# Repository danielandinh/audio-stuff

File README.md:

# audio-stuff
collection of audio circuits/projects

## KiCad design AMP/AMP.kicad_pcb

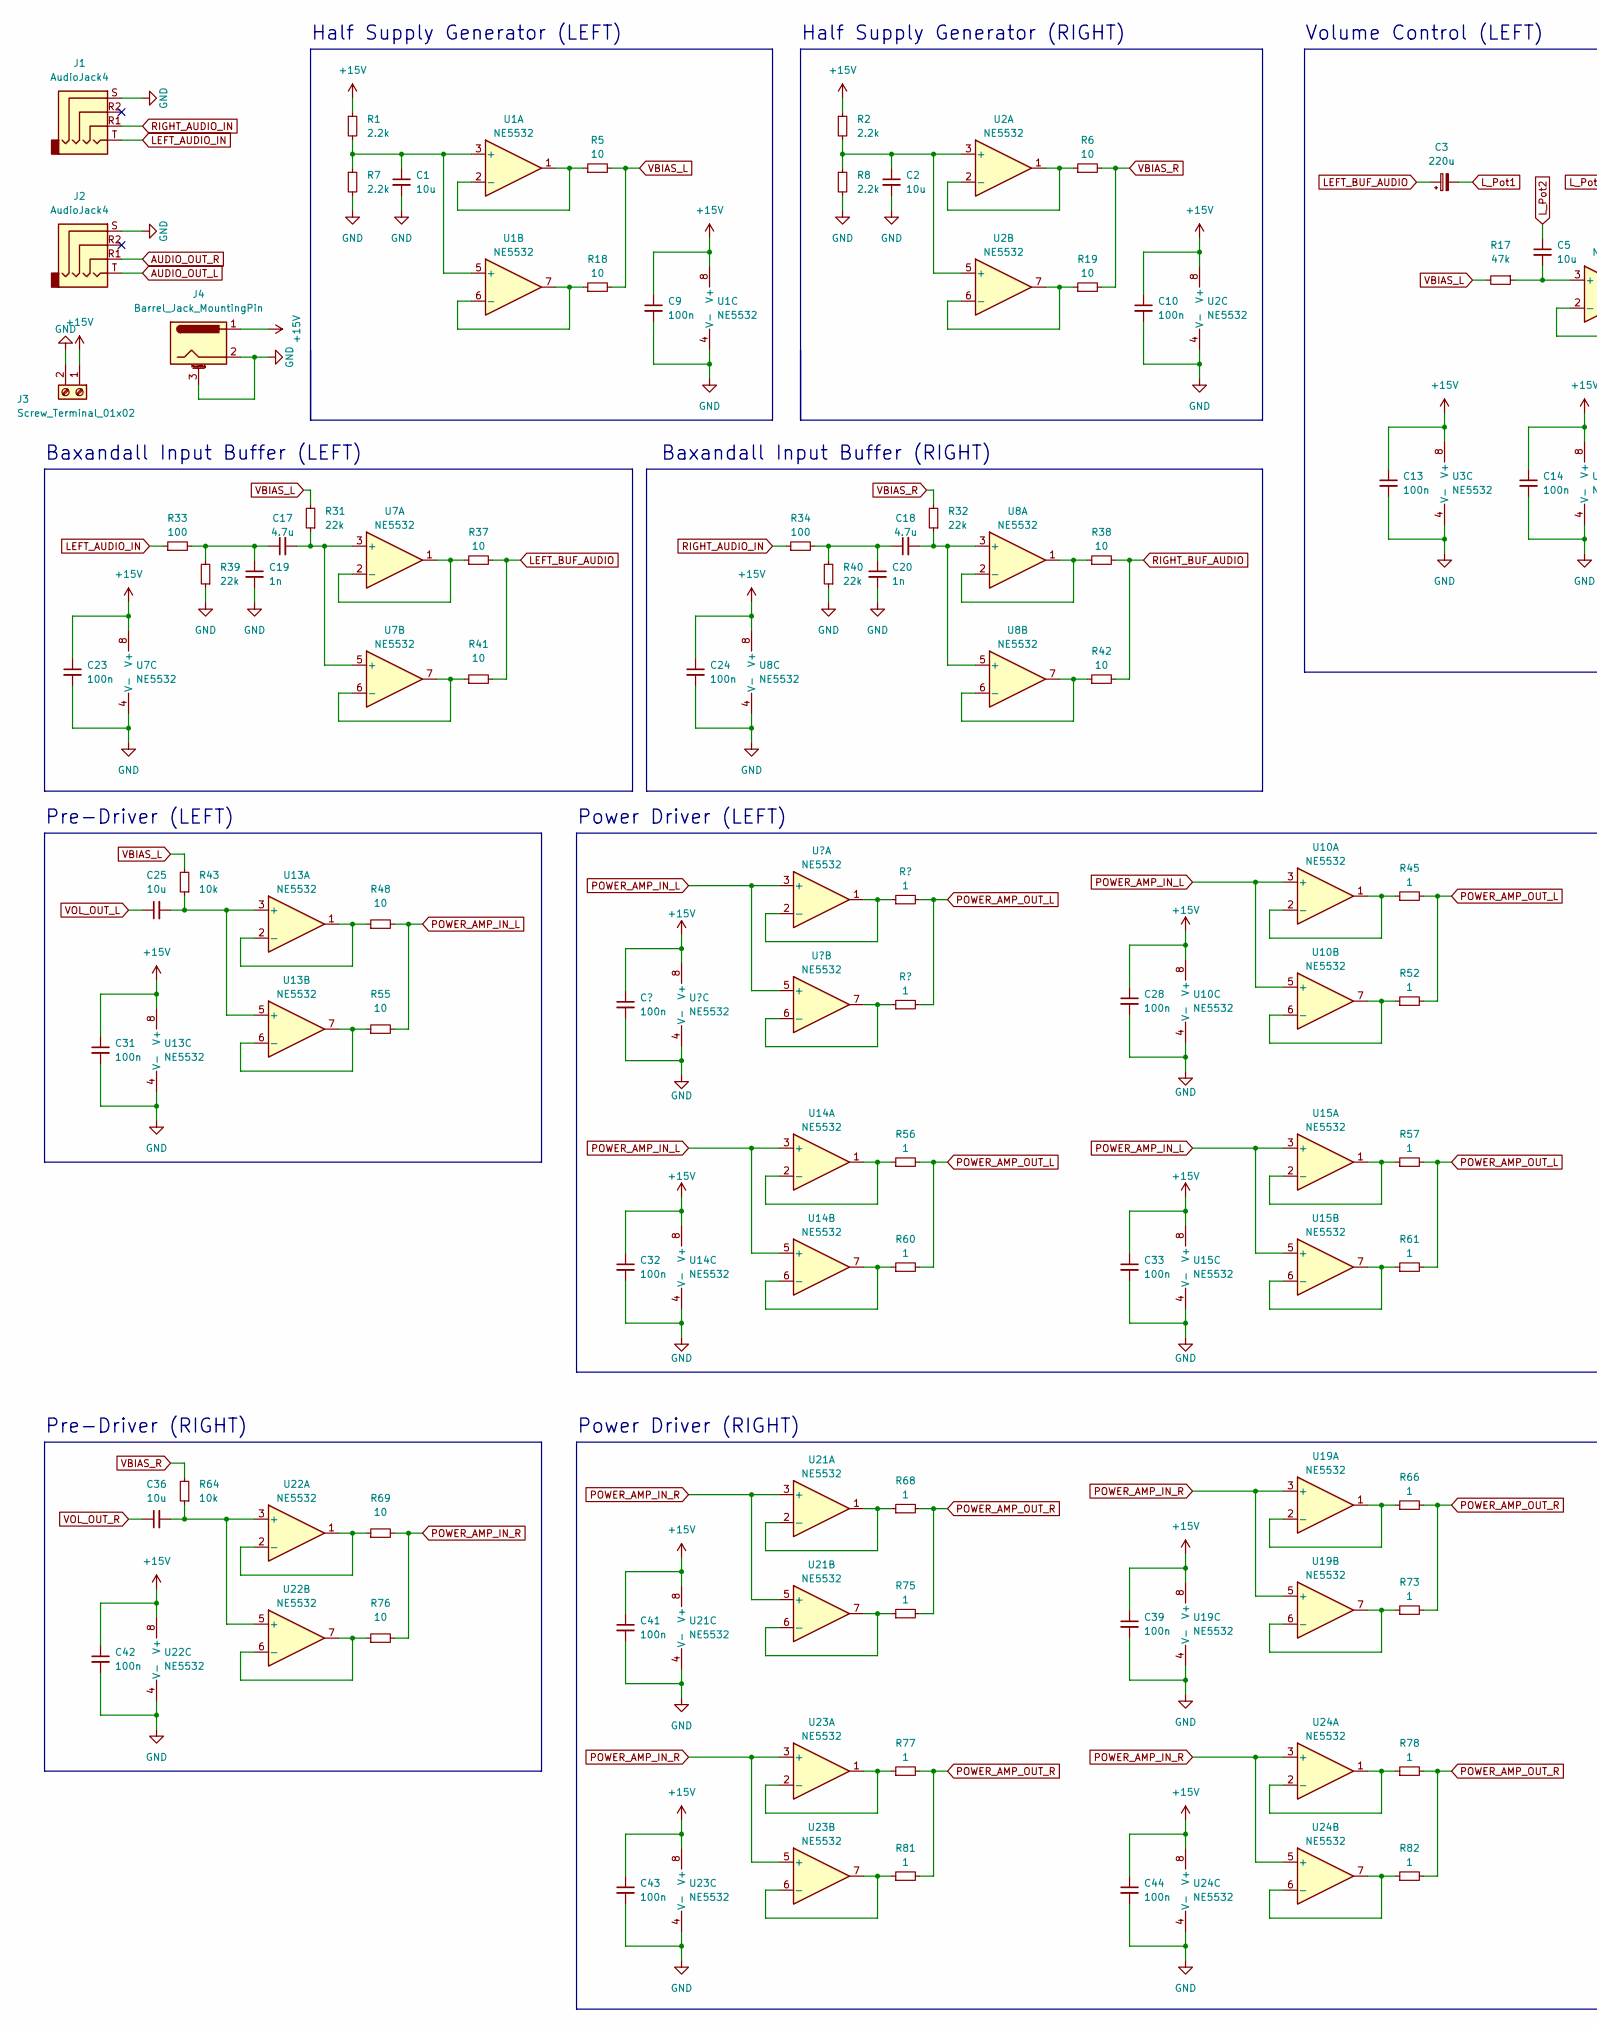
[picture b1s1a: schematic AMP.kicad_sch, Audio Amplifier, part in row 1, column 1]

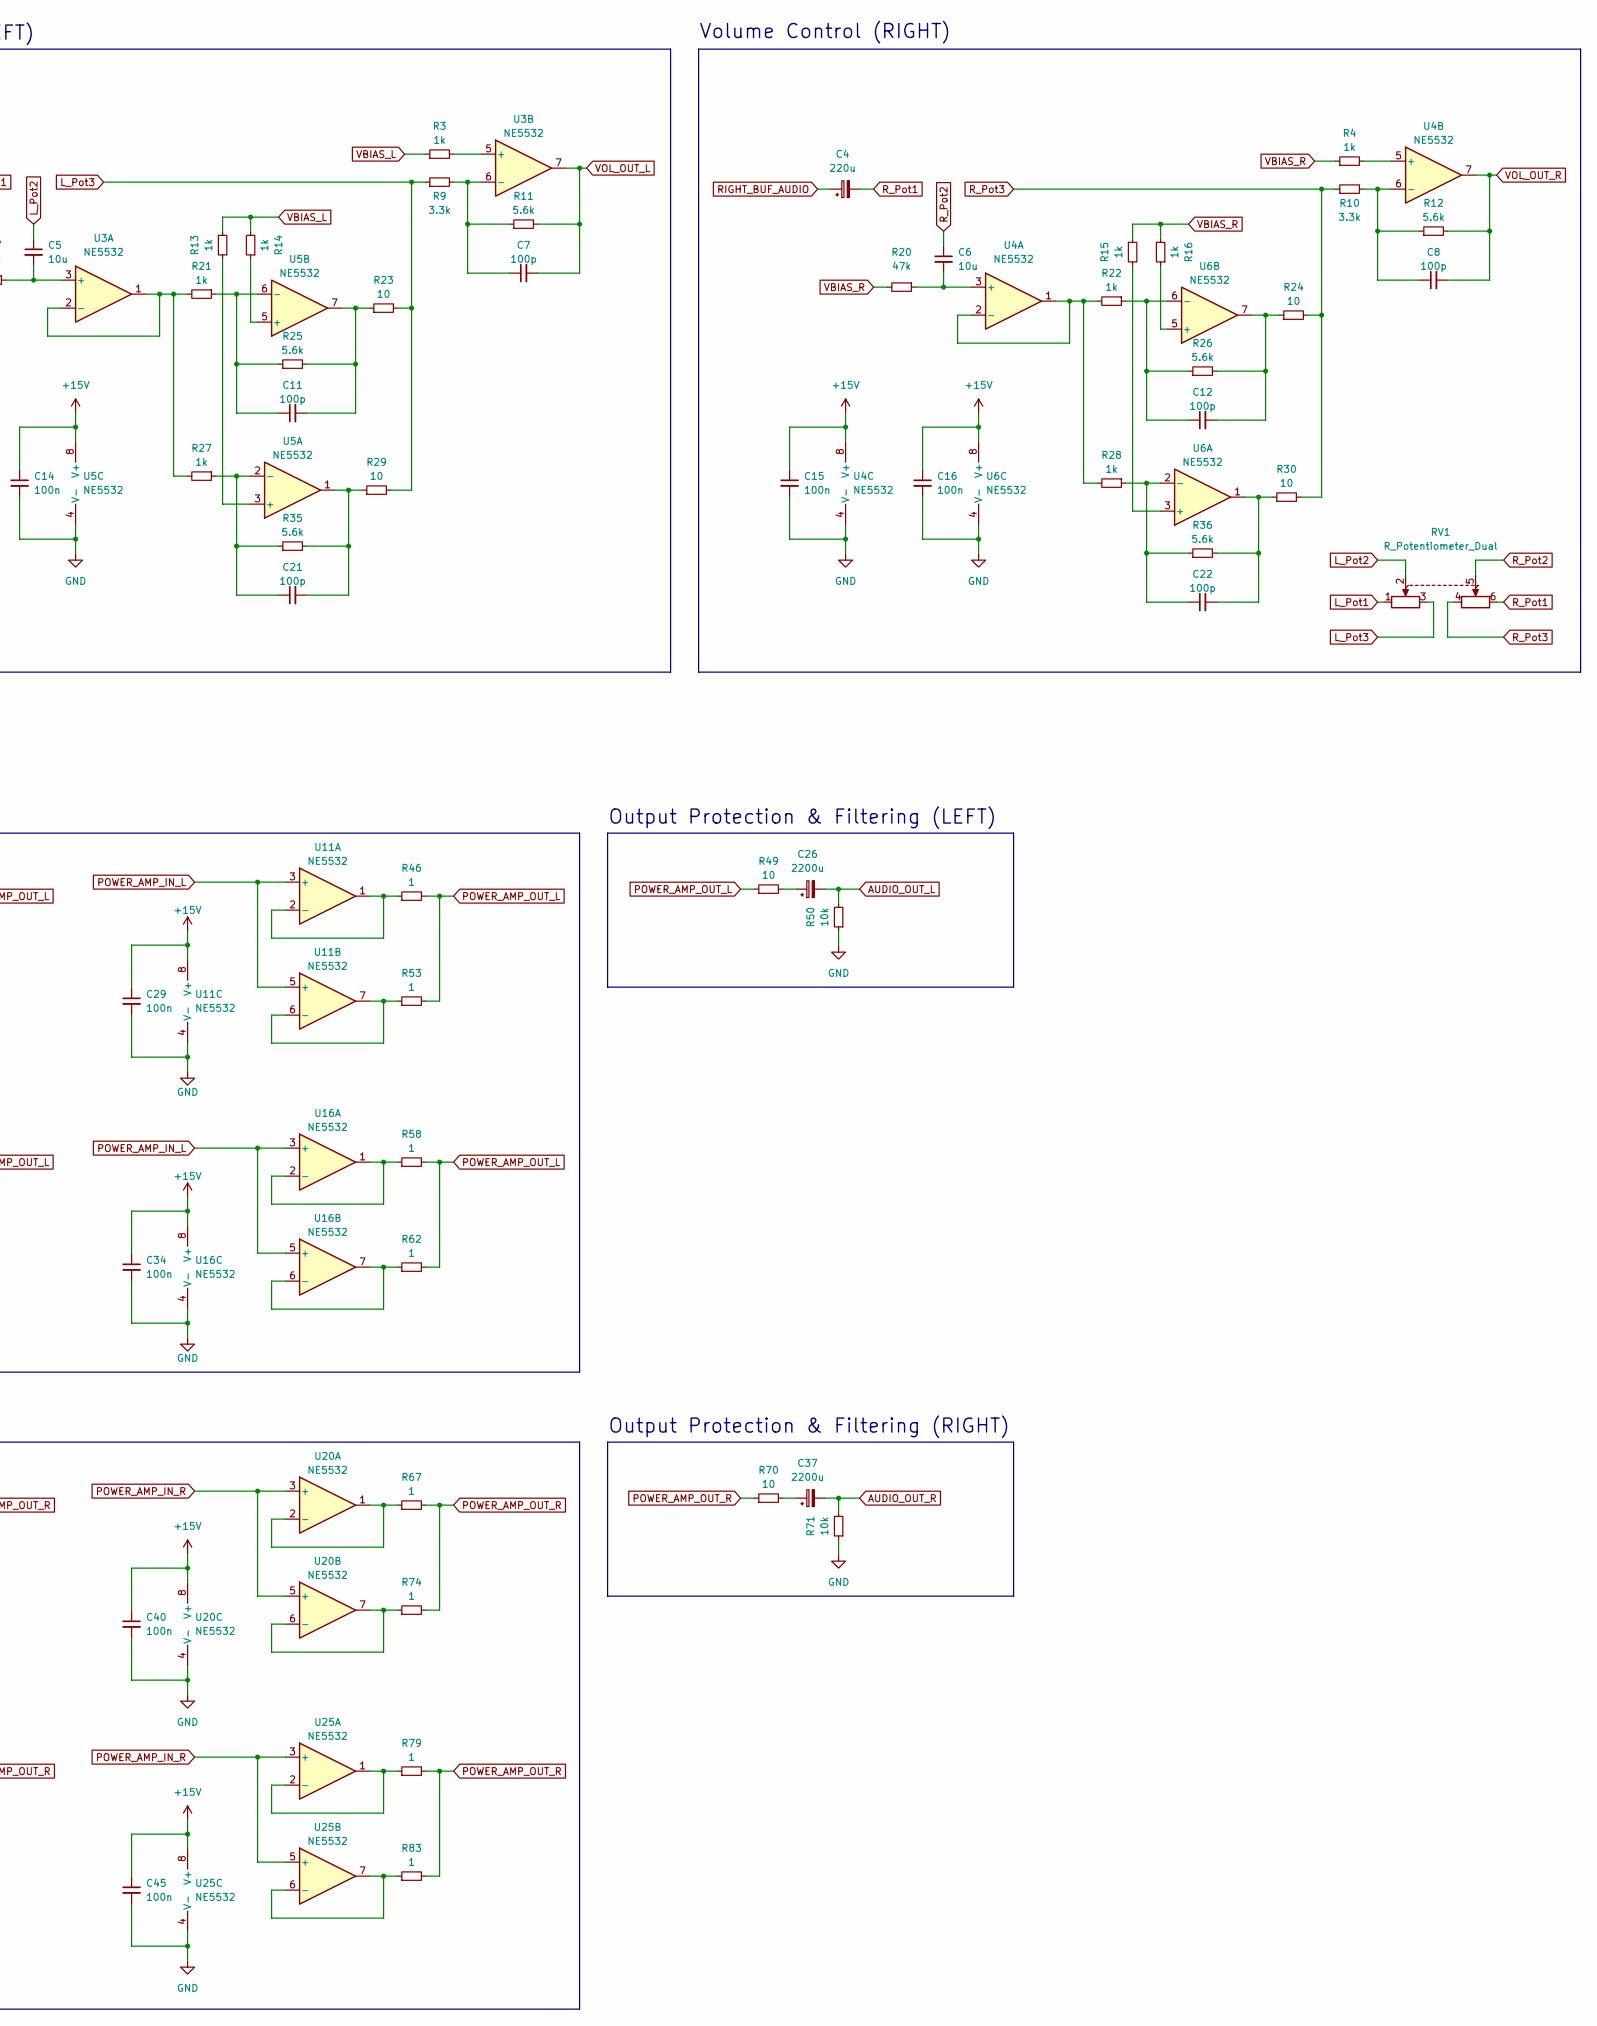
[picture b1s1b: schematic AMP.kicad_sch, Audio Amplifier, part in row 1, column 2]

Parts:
C1, C2, C5, C6: 10u; R_0603_1608Metric; LCSC C96446
C3, C4: 220u; CP_Radial_D6.3mm_P2.50mm; LCSC C2831780
C7, C8, C11, C12, C21, C22: 100p; R_0603_1608Metric; LCSC C14858
C9, C10, C13, C14, C15, C16, C23, C24, C28, C29, C31, C32, C33, C34, C39, C40, C41, C42, C43, C44, C45: 100n; R_0603_1608Metric; LCSC C14663
C17, C18: 4.7u; C_Rect_L24.0mm_W12.8mm_P22.50mm_MKT; LCSC C3019077
C19, C20: 1n; C_0201_0603Metric; LCSC C1588
C25, C36: 10u; C_Axial_L22.0mm_D10.5mm_P27.50mm_Horizontal; LCSC C5116053
C26, C37: 2200u; CP_Radial_D12.5mm_P5.00mm; LCSC C5329685
J1, J2: AudioJack4; Jack_3.5mm_PJ320D_Horizontal; LCSC C431535
J3: Screw_Terminal_01x02; TerminalBlock_bornier-2_P5.08mm; LCSC C430601
J4: Barrel_Jack_MountingPin; BarrelJack_Horizontal; LCSC C319098
R1, R2, R7, R8: 2.2k; R_0603_1608Metric; LCSC C557651
R3, R4, R13, R14, R15, R16, R21, R22, R27, R28: 1k; R_0603_1608Metric; LCSC C110776
R5, R6, R18, R19, R23, R24, R29, R30, R37, R38, R41, R42, R48, R49, R55, R69, R70, R76: 10; R_0603_1608Metric; LCSC C319922
R9, R10: 3.3k; R_1206_3216Metric; LCSC C706452
R11, R12, R25, R26, R35, R36: 5.6k; R_0603_1608Metric; LCSC C445632
R17, R20: 47k; R_0603_1608Metric; LCSC C307918
R31, R32, R39, R40: 22k; R_0603_1608Metric; LCSC C375508
R33, R34: 100; R_0603_1608Metric; LCSC C217683
R43, R50, R64, R71: 10k; R_1206_3216Metric; LCSC C406727
R45, R46, R52, R53, R56, R57, R58, R60, R61, R62, R66, R67, R68, R73, R74, R75, R77, R78, R79, R81, R82, R83: 1; R_1206_3216Metric; LCSC C111291
RV1: R_Potentiometer_Dual; Potentiometer_Alps_RK163_Dual_Horizontal
U1, U2, U3, U4, U5, U6, U7, U8, U10, U11, U13, U14, U15, U16, U19, U20, U21, U22, U23, U24, U25: NE5532; NE5532DR; LCSC C7426

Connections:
+15V: C9.1, C10.1, C13.1, C14.1, C15.1, C16.1, C23.1, C24.1, C28.1, C29.1, C31.1, C32.1, C33.1, C34.1, C39.1, C40.1, C41.1, C42.1, C43.1, C44.1, C45.1, J3.1, J4.1, R1.1, R2.1, U1.8 (V+), U2.8 (V+), U3.8 (V+), U4.8 (V+), U5.8 (V+), U6.8 (V+), U7.8 (V+), U8.8 (V+), U10.8 (V+), U11.8 (V+), U13.8 (V+), U14.8 (V+), U15.8 (V+), U16.8 (V+), U19.8 (V+), U20.8 (V+), U21.8 (V+), U22.8 (V+), U23.8 (V+), U24.8 (V+), U25.8 (V+); also elsewhere on the board
AUDIO_OUT_L: C26.2, J2.T, R50.2
AUDIO_OUT_R: C37.2, J2.R1, R71.2
GND: C1.2, C2.2, C9.2, C10.2, C13.2, C14.2, C15.2, C16.2, C19.2, C20.2, C23.2, C24.2, C28.2, C29.2, C31.2, C32.2, C33.2, C34.2, C39.2, C40.2, C41.2, C42.2, C43.2, C44.2, C45.2, J1.S, J2.S, J3.2, J4.2, J4.3 (MountPin), R7.2, R8.2, R39.1, R40.1, R50.1, R71.1, U1.4 (V-), U2.4 (V-), U3.4 (V-), U4.4 (V-), U5.4 (V-), U6.4 (V-), U7.4 (V-), U8.4 (V-), U10.4 (V-), U11.4 (V-), U13.4 (V-), U14.4 (V-), U15.4 (V-), U16.4 (V-), U19.4 (V-), U20.4 (V-), U21.4 (V-), U22.4 (V-), U23.4 (V-), U24.4 (V-), U25.4 (V-); also elsewhere on the board
LEFT_AUDIO_IN: J1.T, R33.1
LEFT_BUF_AUDIO: C3.1, R37.2, R41.2
L_Pot1: C3.2, RV1.1
L_Pot2: C5.1, RV1.2
L_Pot3: R9.1, R23.2, R29.2, RV1.3
unnamed: C1.1, R1.2, R7.1, U1.3 (+), U1.5 (+)
unnamed: C2.1, R2.2, R8.1, U2.3 (+), U2.5 (+)
unnamed: C5.2, R17.1, U3.3 (+)
unnamed: C6.2, R20.1, U4.3 (+)
unnamed: C7.1, R9.2, R11.1, U3.6 (-)
unnamed: C8.1, R10.2, R12.1, U4.6 (-)
unnamed: C11.1, R21.1, R25.1, U5.6 (-)
unnamed: C11.2, R23.1, R25.2, U5.7
unnamed: C12.1, R22.1, R26.1, U6.6 (-)
unnamed: C12.2, R24.1, R26.2, U6.7
unnamed: C17.1, C19.1, R33.2, R39.2
unnamed: C17.2, R31.1, U7.3 (+), U7.5 (+)
unnamed: C18.1, C20.1, R34.2, R40.2
unnamed: C18.2, R32.1, U8.3 (+), U8.5 (+)
unnamed: C21.1, R27.1, R35.1, U5.2 (-)
unnamed: C21.2, R29.1, R35.2, U5.1
unnamed: C22.1, R28.1, R36.1, U6.2 (-)
unnamed: C22.2, R30.1, R36.2, U6.1
unnamed: C25.2, R43.1, U13.3 (+), U13.5 (+)
unnamed: C26.1, R49.2
unnamed: C36.2, R64.1, U22.3 (+), U22.5 (+)
unnamed: C37.1, R70.2
unnamed: R3.2, U3.5 (+)
unnamed: R4.2, U4.5 (+)
unnamed: R5.1, U1.1, U1.2 (-)
unnamed: R6.1, U2.1, U2.2 (-)
unnamed: R13.2, U5.3 (+)
unnamed: R14.1, U5.5 (+)
unnamed: R15.2, U6.3 (+)
unnamed: R16.1, U6.5 (+)
unnamed: R18.1, U1.6 (-), U1.7
unnamed: R19.1, U2.6 (-), U2.7
unnamed: R21.2, R27.2, U3.1, U3.2 (-)
unnamed: R22.2, R28.2, U4.1, U4.2 (-)
unnamed: R37.1, U7.1, U7.2 (-)
unnamed: R38.1, U8.1, U8.2 (-)
unnamed: R41.1, U7.6 (-), U7.7
unnamed: R42.1, U8.6 (-), U8.7
unnamed: R45.1, U10.1, U10.2 (-)
unnamed: R46.1, U11.1, U11.2 (-)
unnamed: R48.1, U13.1, U13.2 (-)
unnamed: R52.1, U10.6 (-), U10.7
unnamed: R53.1, U11.6 (-), U11.7
unnamed: R55.1, U13.6 (-), U13.7
unnamed: R56.1, U14.1, U14.2 (-)
unnamed: R57.1, U15.1, U15.2 (-)
unnamed: R58.1, U16.1, U16.2 (-)
unnamed: R60.1, U14.6 (-), U14.7
unnamed: R61.1, U15.6 (-), U15.7
unnamed: R62.1, U16.6 (-), U16.7
unnamed: R66.1, U19.1, U19.2 (-)
unnamed: R67.1, U20.1, U20.2 (-)
unnamed: R68.1, U21.1, U21.2 (-)
unnamed: R69.1, U22.1, U22.2 (-)
unnamed: R73.1, U19.6 (-), U19.7
unnamed: R74.1, U20.6 (-), U20.7
unnamed: R75.1, U21.6 (-), U21.7
unnamed: R76.1, U22.6 (-), U22.7
unnamed: R77.1, U23.1, U23.2 (-)
unnamed: R78.1, U24.1, U24.2 (-)
unnamed: R79.1, U25.1, U25.2 (-)
unnamed: R81.1, U23.6 (-), U23.7
unnamed: R82.1, U24.6 (-), U24.7
unnamed: R83.1, U25.6 (-), U25.7
POWER_AMP_IN_L: R48.2, R55.2, U10.3 (+), U10.5 (+), U11.3 (+), U11.5 (+), U14.3 (+), U14.5 (+), U15.3 (+), U15.5 (+), U16.3 (+), U16.5 (+); also elsewhere on the board
POWER_AMP_IN_R: R69.2, R76.2, U19.3 (+), U19.5 (+), U20.3 (+), U20.5 (+), U21.3 (+), U21.5 (+), U23.3 (+), U23.5 (+), U24.3 (+), U24.5 (+), U25.3 (+), U25.5 (+)
POWER_AMP_OUT_L: R45.2, R46.2, R49.1, R52.2, R53.2, R56.2, R57.2, R58.2, R60.2, R61.2, R62.2; also elsewhere on the board
POWER_AMP_OUT_R: R66.2, R67.2, R68.2, R70.1, R73.2, R74.2, R75.2, R77.2, R78.2, R79.2, R81.2, R82.2, R83.2
RIGHT_AUDIO_IN: J1.R1, R34.1
RIGHT_BUF_AUDIO: C4.1, R38.2, R42.2
R_Pot1: C4.2, RV1.6
R_Pot2: C6.1, RV1.5
R_Pot3: R10.1, R24.2, R30.2, RV1.4
VBIAS_L: R3.1, R5.2, R13.1, R14.2, R17.2, R18.2, R31.2, R43.2
VBIAS_R: R4.1, R6.2, R15.1, R16.2, R19.2, R20.2, R32.2, R64.2
VOL_OUT_L: C7.2, C25.1, R11.2, U3.7
VOL_OUT_R: C8.2, C36.1, R12.2, U4.7

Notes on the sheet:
Baxandall Input Buffer (RIGHT)
Volume Control (LEFT)
Half Supply Generator (LEFT)
Output Protection & Filtering (RIGHT)
Pre-Driver (LEFT)
Output Protection & Filtering (LEFT)
Pre-Driver (RIGHT)
Power Driver (RIGHT)
Baxandall Input Buffer (LEFT)
Half Supply Generator (RIGHT)
Volume Control (RIGHT)
Power Driver (LEFT)

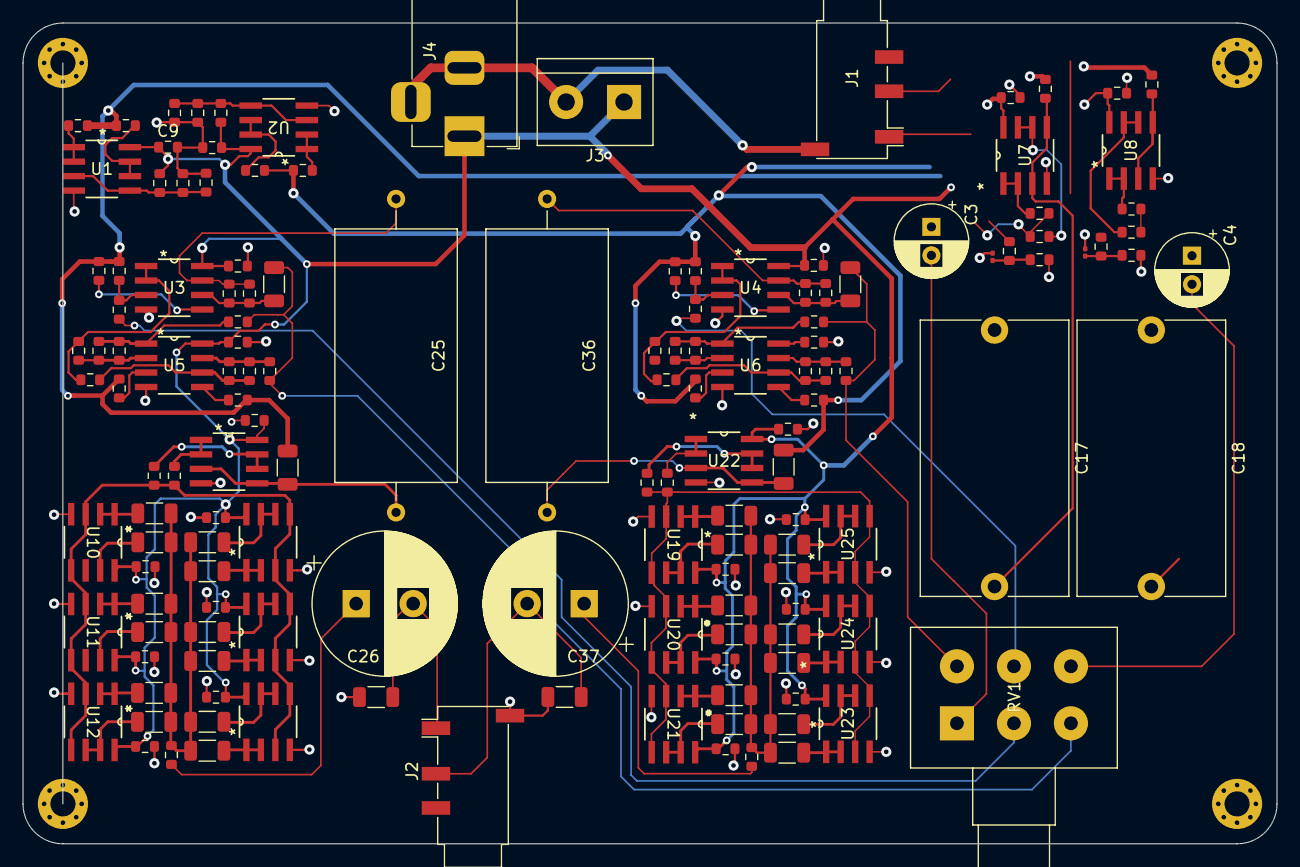
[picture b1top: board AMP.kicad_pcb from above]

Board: 4 copper layers, 110.0 x 72.0 mm, 145 parts (0 on the bottom side), 88 nets.

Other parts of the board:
C30: 100n; R_0603_1608Metric
R47, R54: 1; R_1206_3216Metric
U12: NE5532; NE5532DR

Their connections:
+15V: C30.1, U12.8 (V+); also elsewhere on the board
GND: C30.2, U12.4 (V-); also elsewhere on the board
unnamed: R47.1, U12.1, U12.2 (-)
unnamed: R54.1, U12.6 (-), U12.7
POWER_AMP_IN_L: U12.3 (+), U12.5 (+); also elsewhere on the board
POWER_AMP_OUT_L: R47.2, R54.2; also elsewhere on the board

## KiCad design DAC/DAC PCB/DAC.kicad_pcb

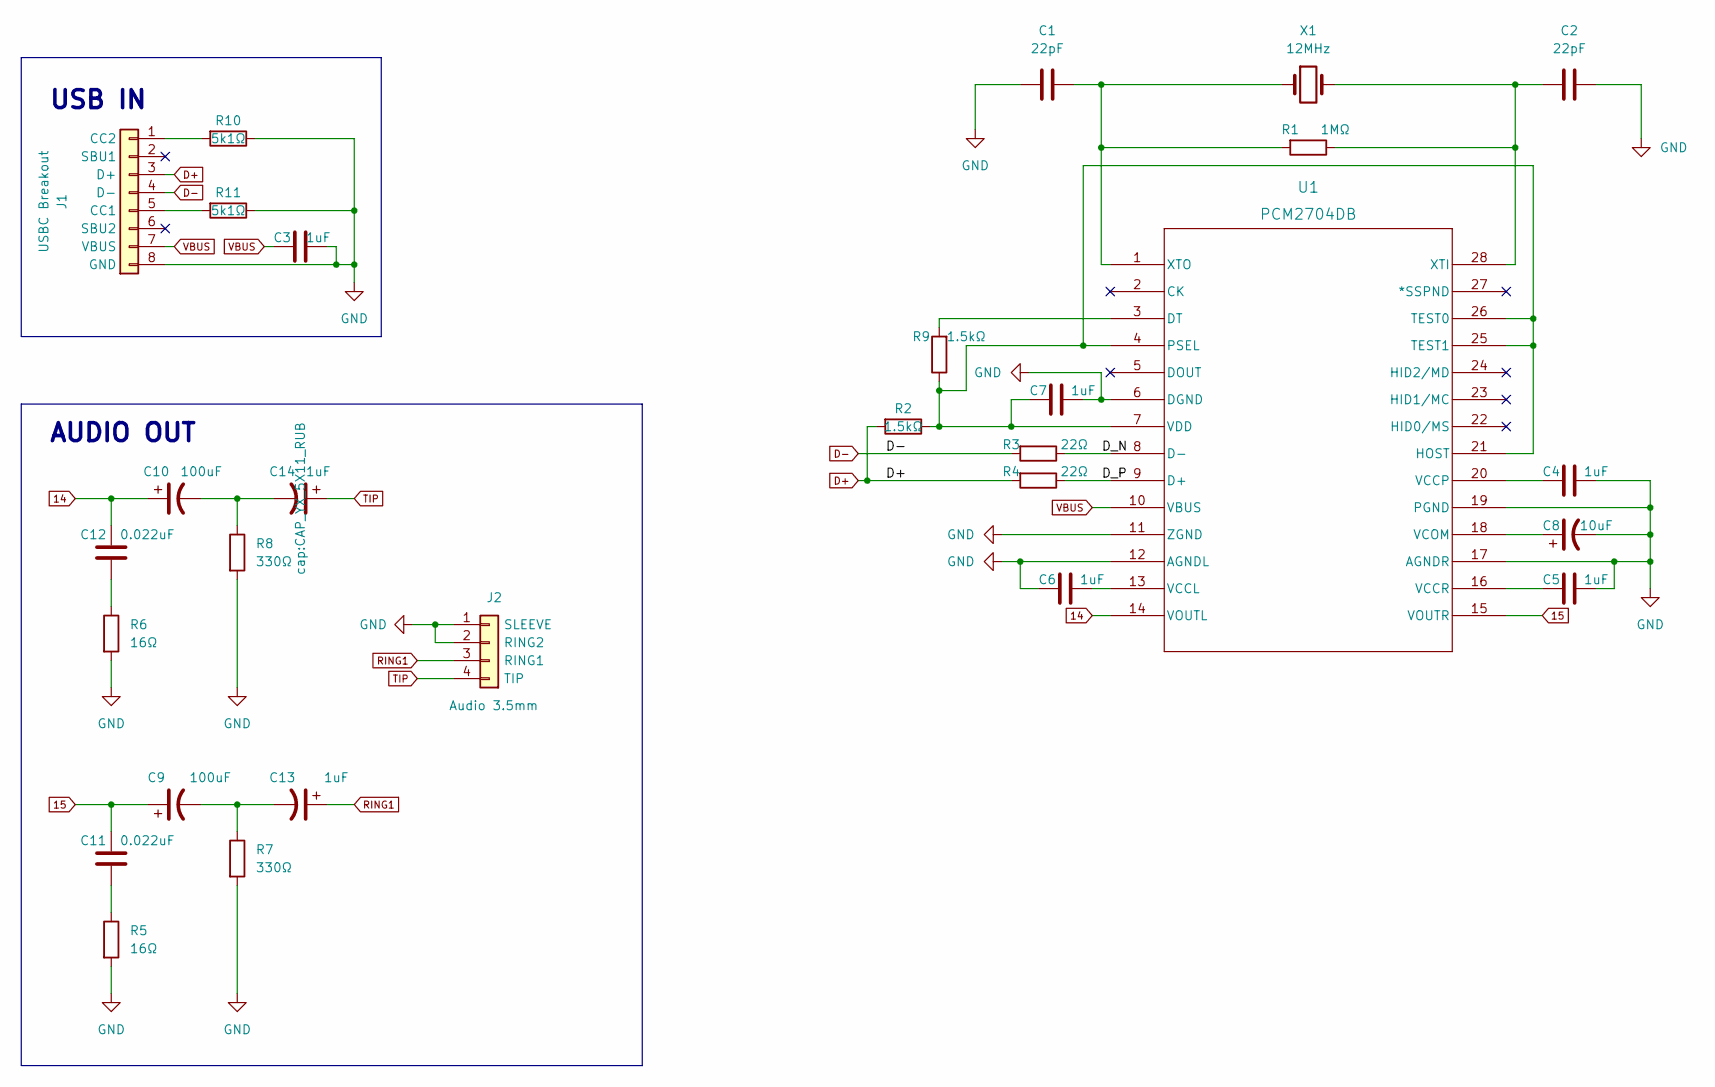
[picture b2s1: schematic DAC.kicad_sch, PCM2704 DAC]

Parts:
C1, C2: 22pF; C_Disc_D5.0mm_W2.5mm_P2.50mm
C3, C4, C5, C6, C7: 1uF; C_Disc_D5.0mm_W2.5mm_P2.50mm
C8: 10uF; CAP_YX_5X11_RUB
C9, C10: 100uF; cap big
C11, C12: 0.022uF; C_Disc_D5.0mm_W2.5mm_P2.50mm
C13, C14: 1uF; CAP_YX_5X11_RUB
J1: USBC Breakout; usb c breadboard 01x08
J2: Audio 3.5mm; headphone jack breadboard
R1: 1MΩ; R_Axial_DIN0207_L6.3mm_D2.5mm_P10.16mm_Horizontal
R2, R9: 1.5kΩ; R_Axial_DIN0204_L3.6mm_D1.6mm_P5.08mm_Horizontal
R3, R4: 22Ω; R_Axial_DIN0207_L6.3mm_D2.5mm_P10.16mm_Horizontal
R5, R6: 16Ω; R_Axial_DIN0207_L6.3mm_D2.5mm_P10.16mm_Horizontal
R7, R8: 330Ω; R_Axial_DIN0207_L6.3mm_D2.5mm_P10.16mm_Horizontal
R10, R11: 5k1Ω; R_Axial_DIN0207_L6.3mm_D2.5mm_P10.16mm_Horizontal
U1: PCM2704DB; DB28_TEX
X1: 12MHz; Crystal_HC49-4H_Vertical

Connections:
14: C10.1, C12.2, U1.14 (VOUTL)
15: C9.1, C11.2, U1.15 (VOUTR)
/D_N: R3.1, U1.8 (D-)
/D_P: R4.1, U1.9 (D+)
D+: J1.3 (D+), R2.2, R4.2
D-: J1.4 (D-), R3.2
GND: C1.1, C2.2, C3.2, C4.2, C5.2, C6.1, C7.2, C8.2, J1.8 (GND), J2.1 (SLEEVE), J2.2 (RING2), R5.2, R6.2, R7.2, R8.2, R10.1, R11.1, U1.6 (DGND), U1.11 (ZGND), U1.12 (AGNDL), U1.17 (AGNDR), U1.19 (PGND)
unnamed: C1.2, R1.2, U1.1 (XTO), X1.1
unnamed: C2.1, R1.1, U1.28 (XTI), X1.2
unnamed: C4.1, U1.20 (VCCP)
unnamed: C5.1, U1.16 (VCCR)
unnamed: C6.2, U1.13 (VCCL)
unnamed: C7.1, R2.1, R9.1, U1.4 (PSEL), U1.7 (VDD), U1.21 (HOST), U1.25 (TEST1), U1.26 (TEST0)
unnamed: C8.1, U1.18 (VCOM)
unnamed: C10.2, C14.2, R8.1
unnamed: C11.1, R5.1
unnamed: C12.1, R6.1
unnamed: C9.2, C13.2, R7.1
unnamed: J1.1 (CC2), R10.2
unnamed: J1.5 (CC1), R11.2
unnamed: R9.2, U1.3 (DT)
RING1: C13.1, J2.3 (RING1)
TIP: C14.1, J2.4 (TIP)
VBUS: C3.1, J1.7 (VBUS), U1.10 (VBUS)

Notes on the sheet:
USB IN
AUDIO OUT

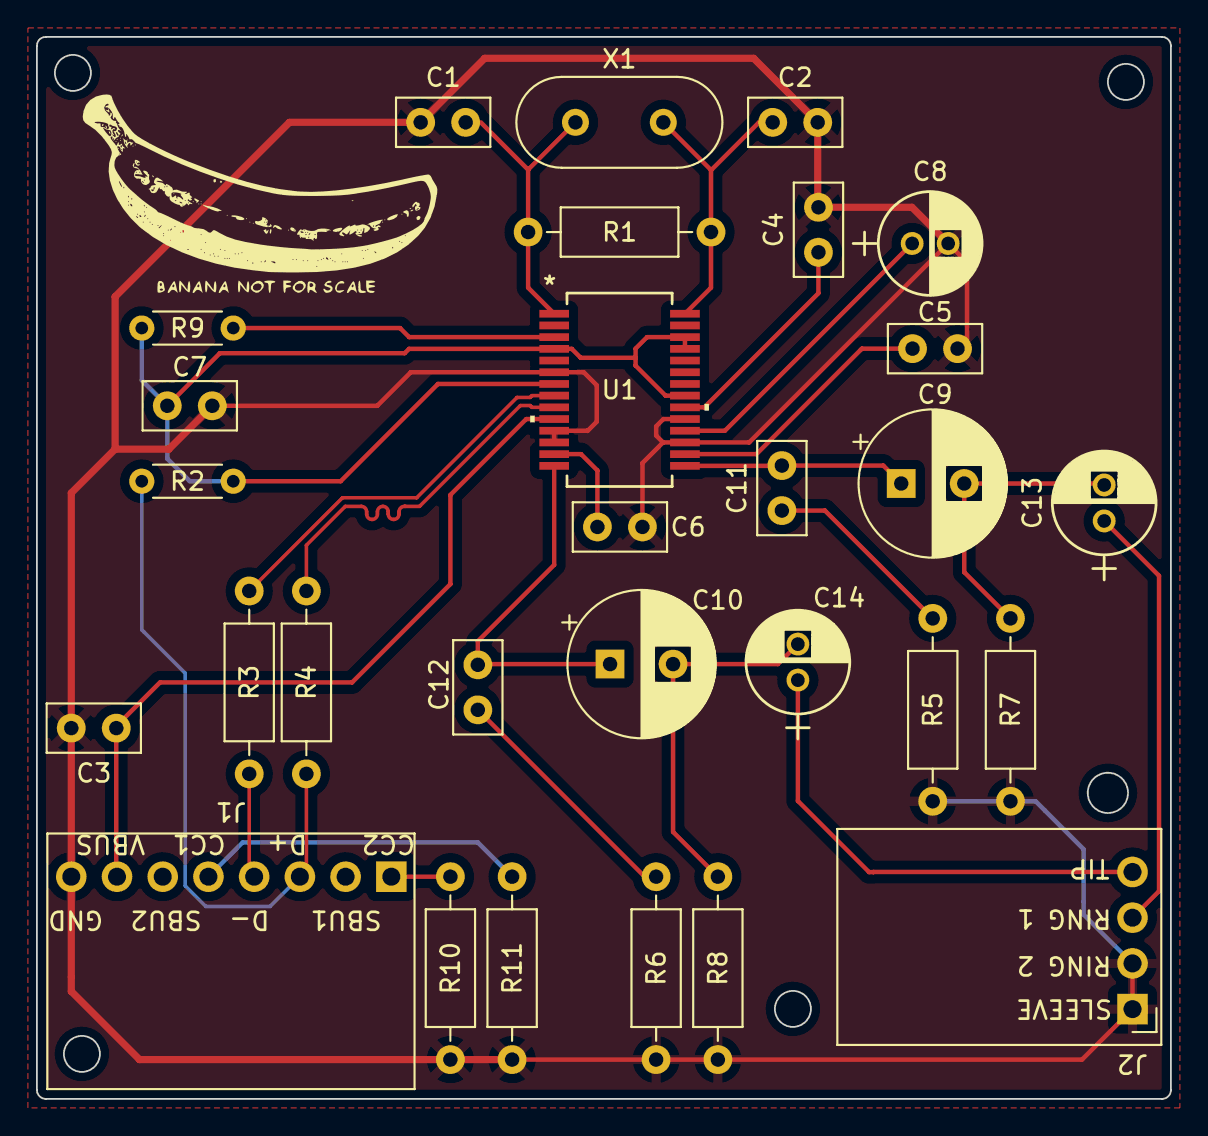
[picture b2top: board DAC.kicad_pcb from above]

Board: 2 copper layers, 63.0 x 59.0 mm, 29 parts (0 on the bottom side), 24 nets.

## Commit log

2023-07-12 pcb for dac
2023-07-19 updated cad files - model + enclosure
2023-07-20 updated tolerances for enclosure
2023-07-30 amp design files
2023-07-31 amp updated files
2023-08-02 schematic done
2023-08-05 pcb layout
2023-08-06 updated files
2023-08-09 pcb layout complete
2023-08-23 Updated AMP PCB
    - added silkscreen
    - added cad models for 3d view
    - convert to kicad 7.0
2023-08-30 updated amp 3d model
